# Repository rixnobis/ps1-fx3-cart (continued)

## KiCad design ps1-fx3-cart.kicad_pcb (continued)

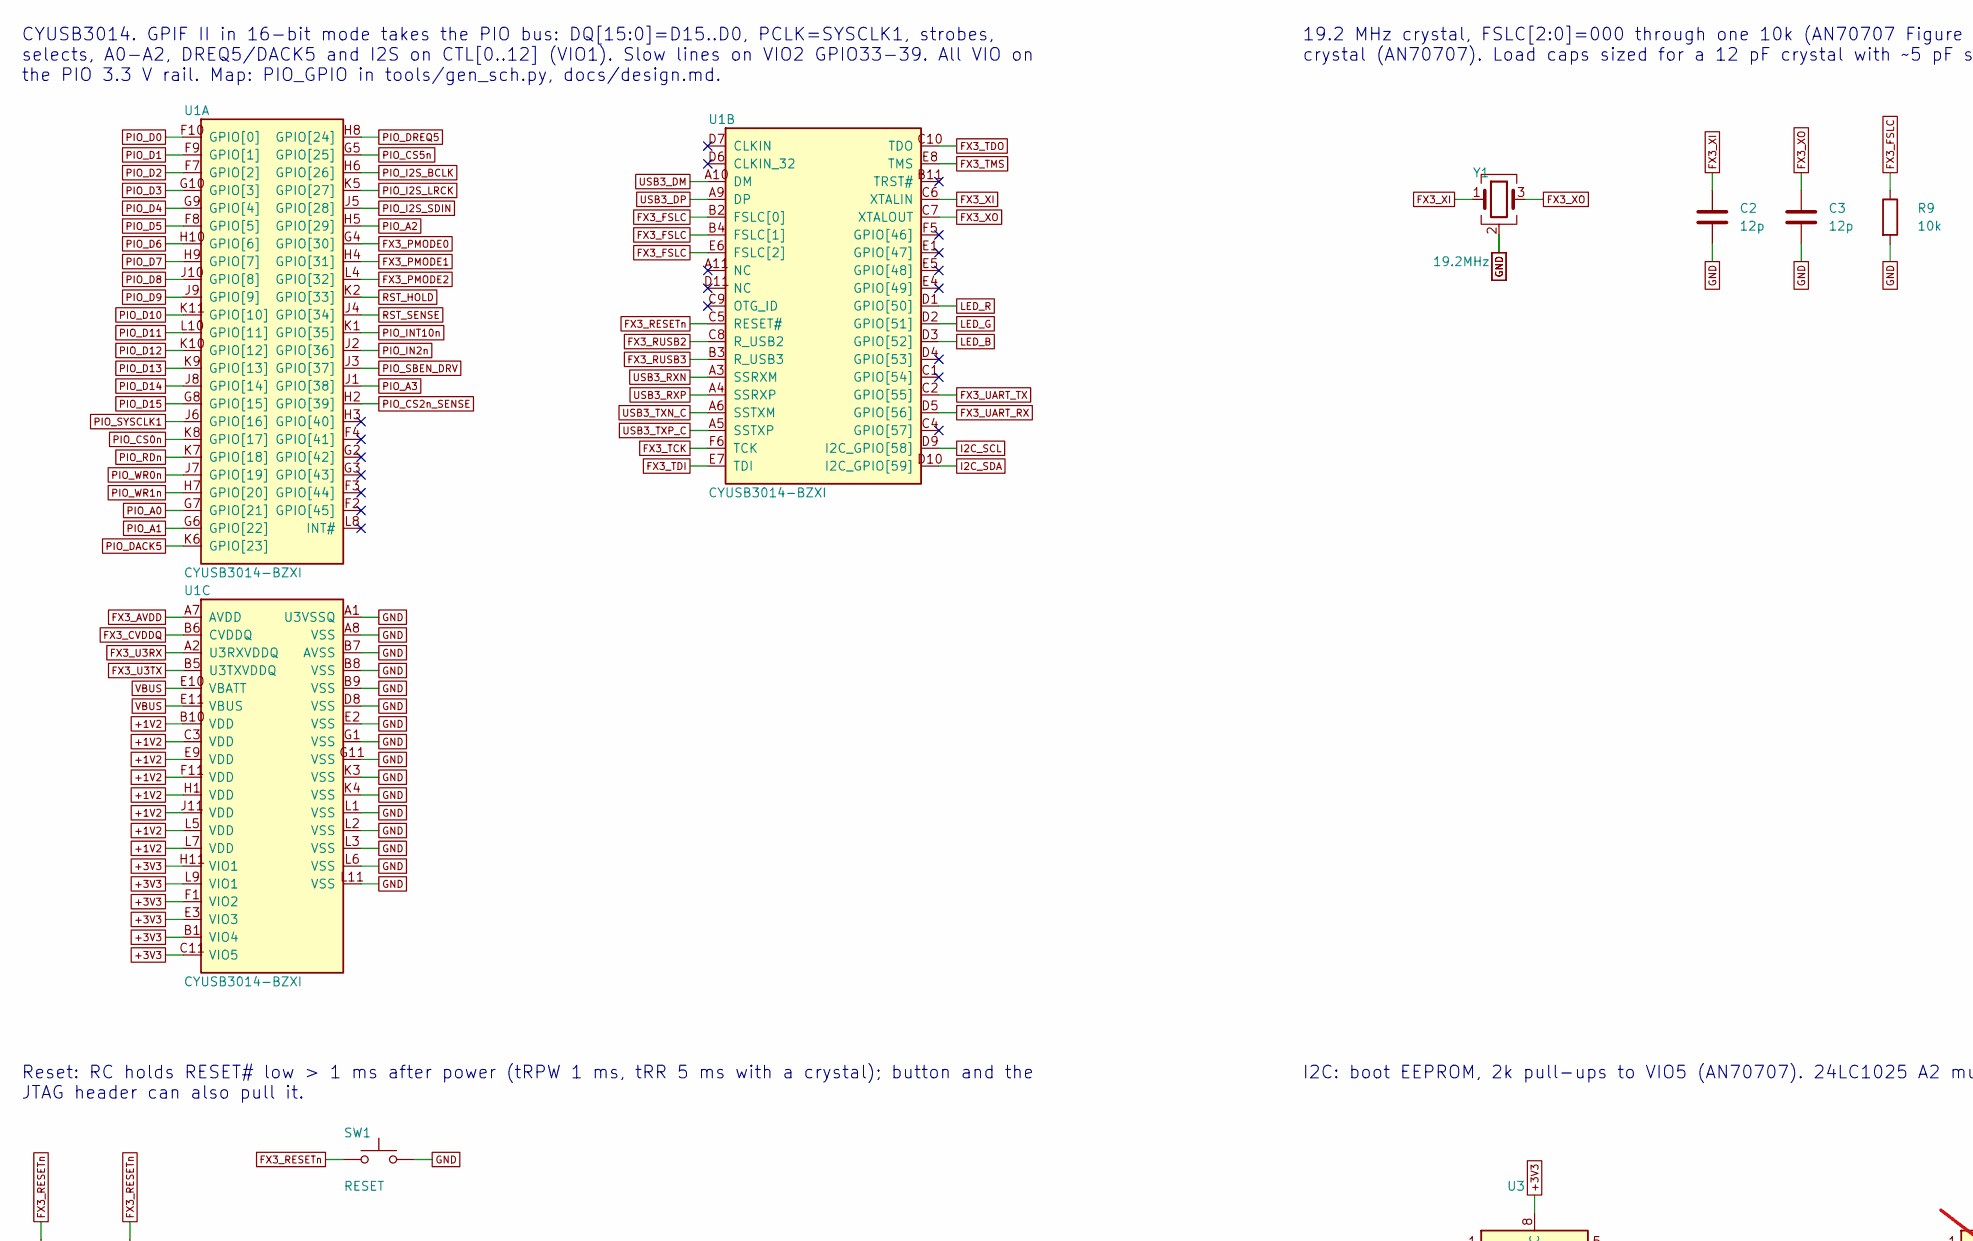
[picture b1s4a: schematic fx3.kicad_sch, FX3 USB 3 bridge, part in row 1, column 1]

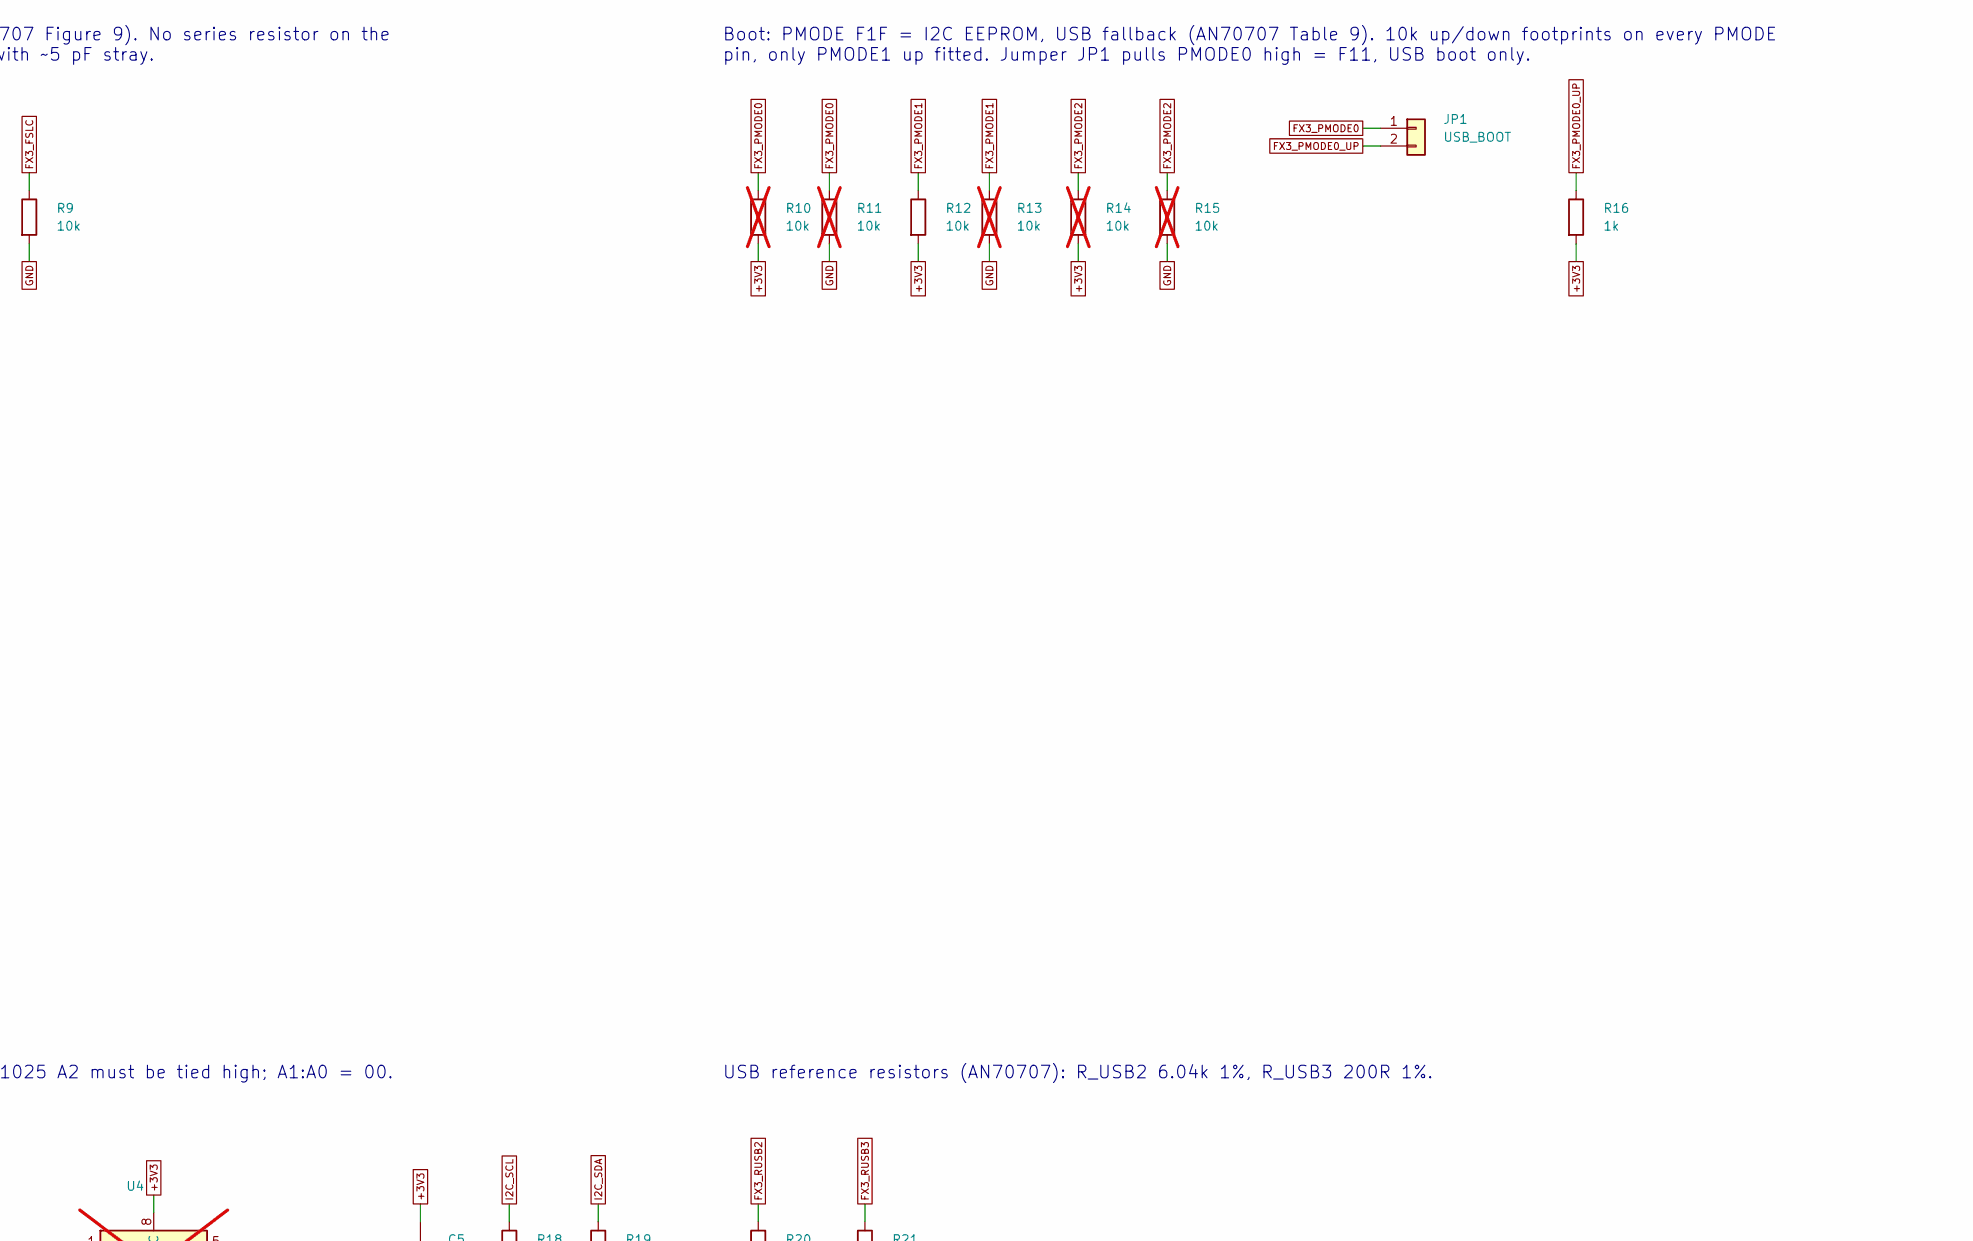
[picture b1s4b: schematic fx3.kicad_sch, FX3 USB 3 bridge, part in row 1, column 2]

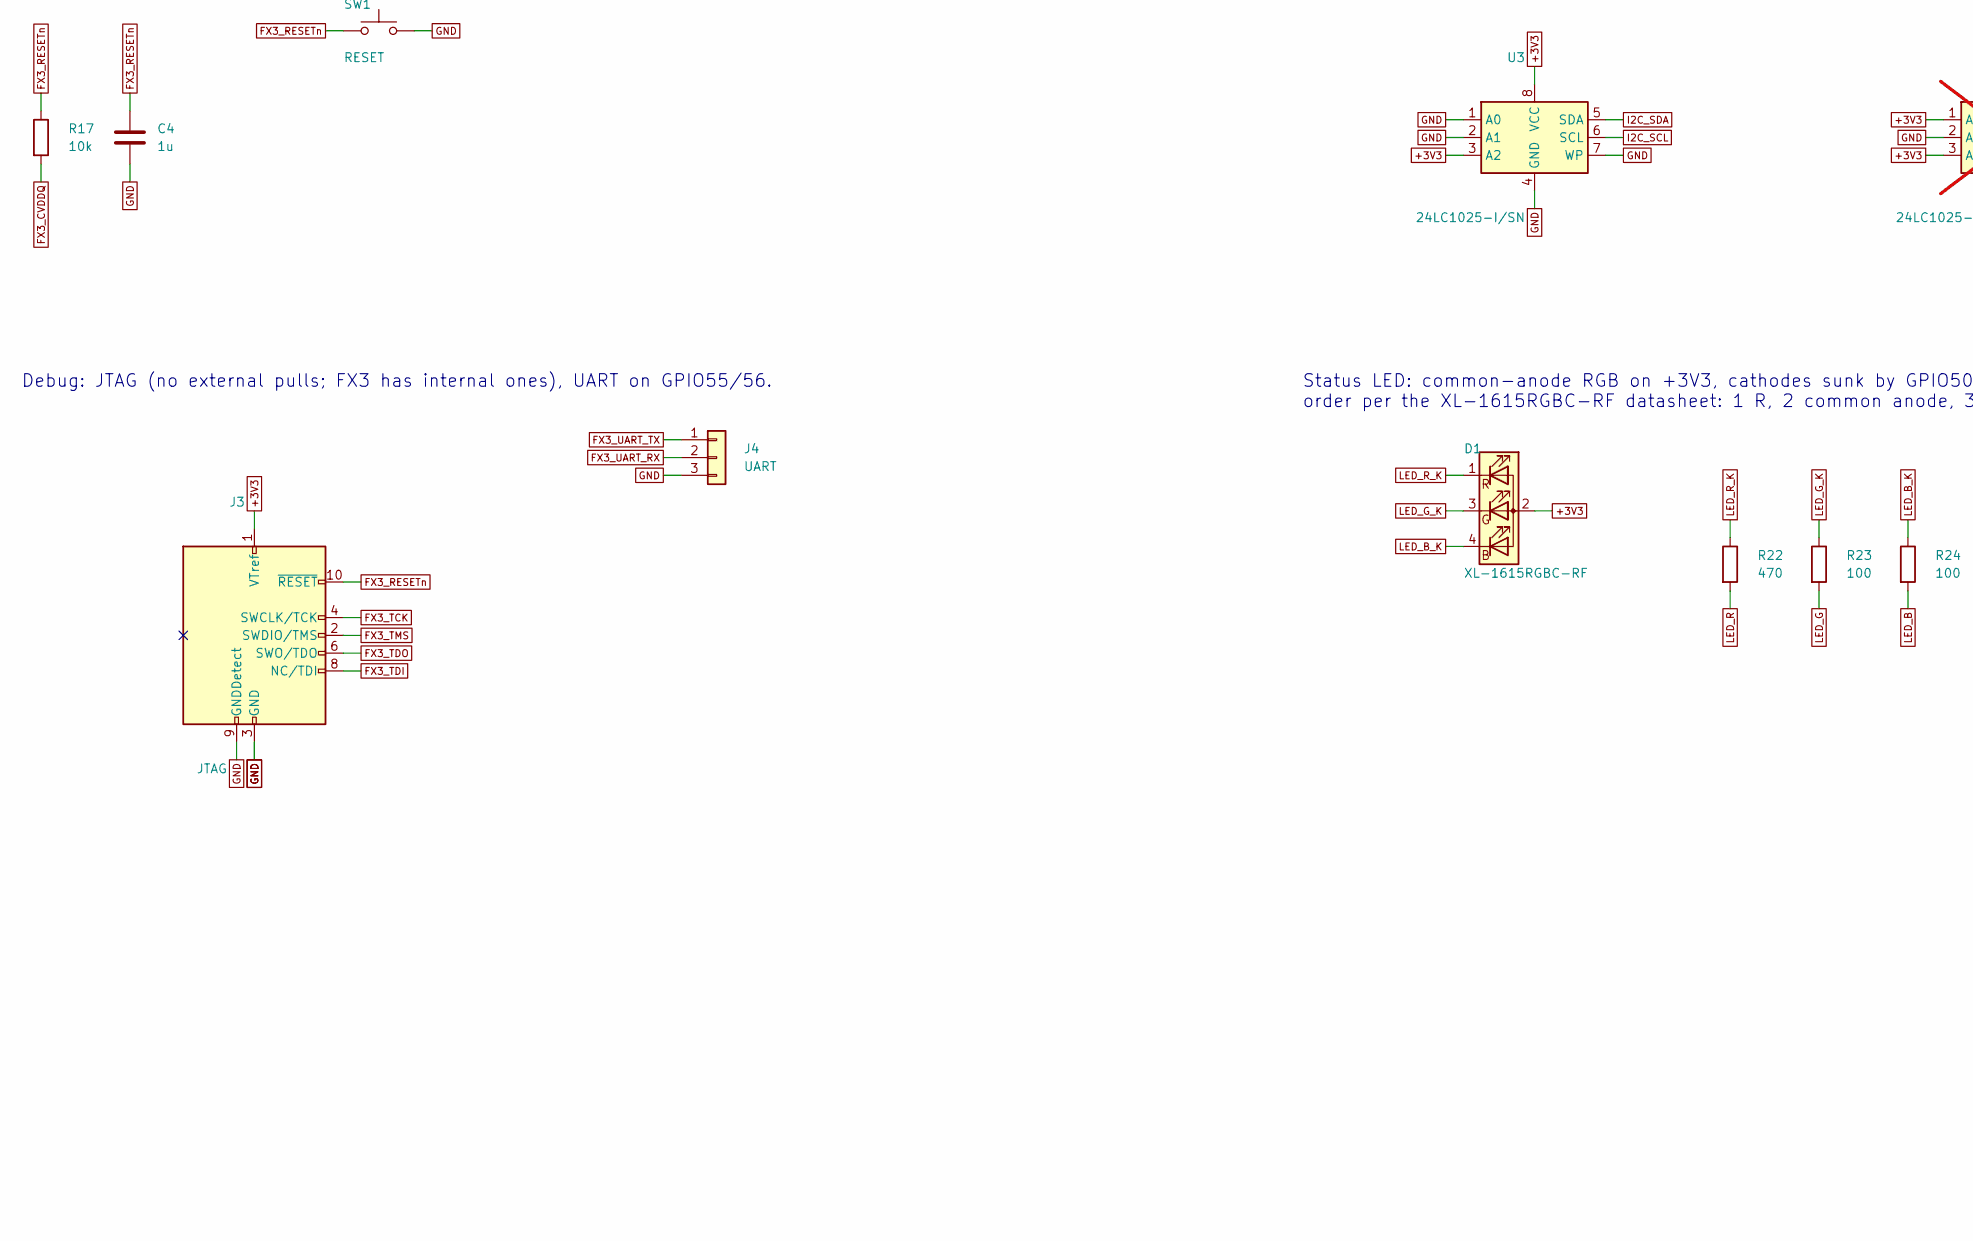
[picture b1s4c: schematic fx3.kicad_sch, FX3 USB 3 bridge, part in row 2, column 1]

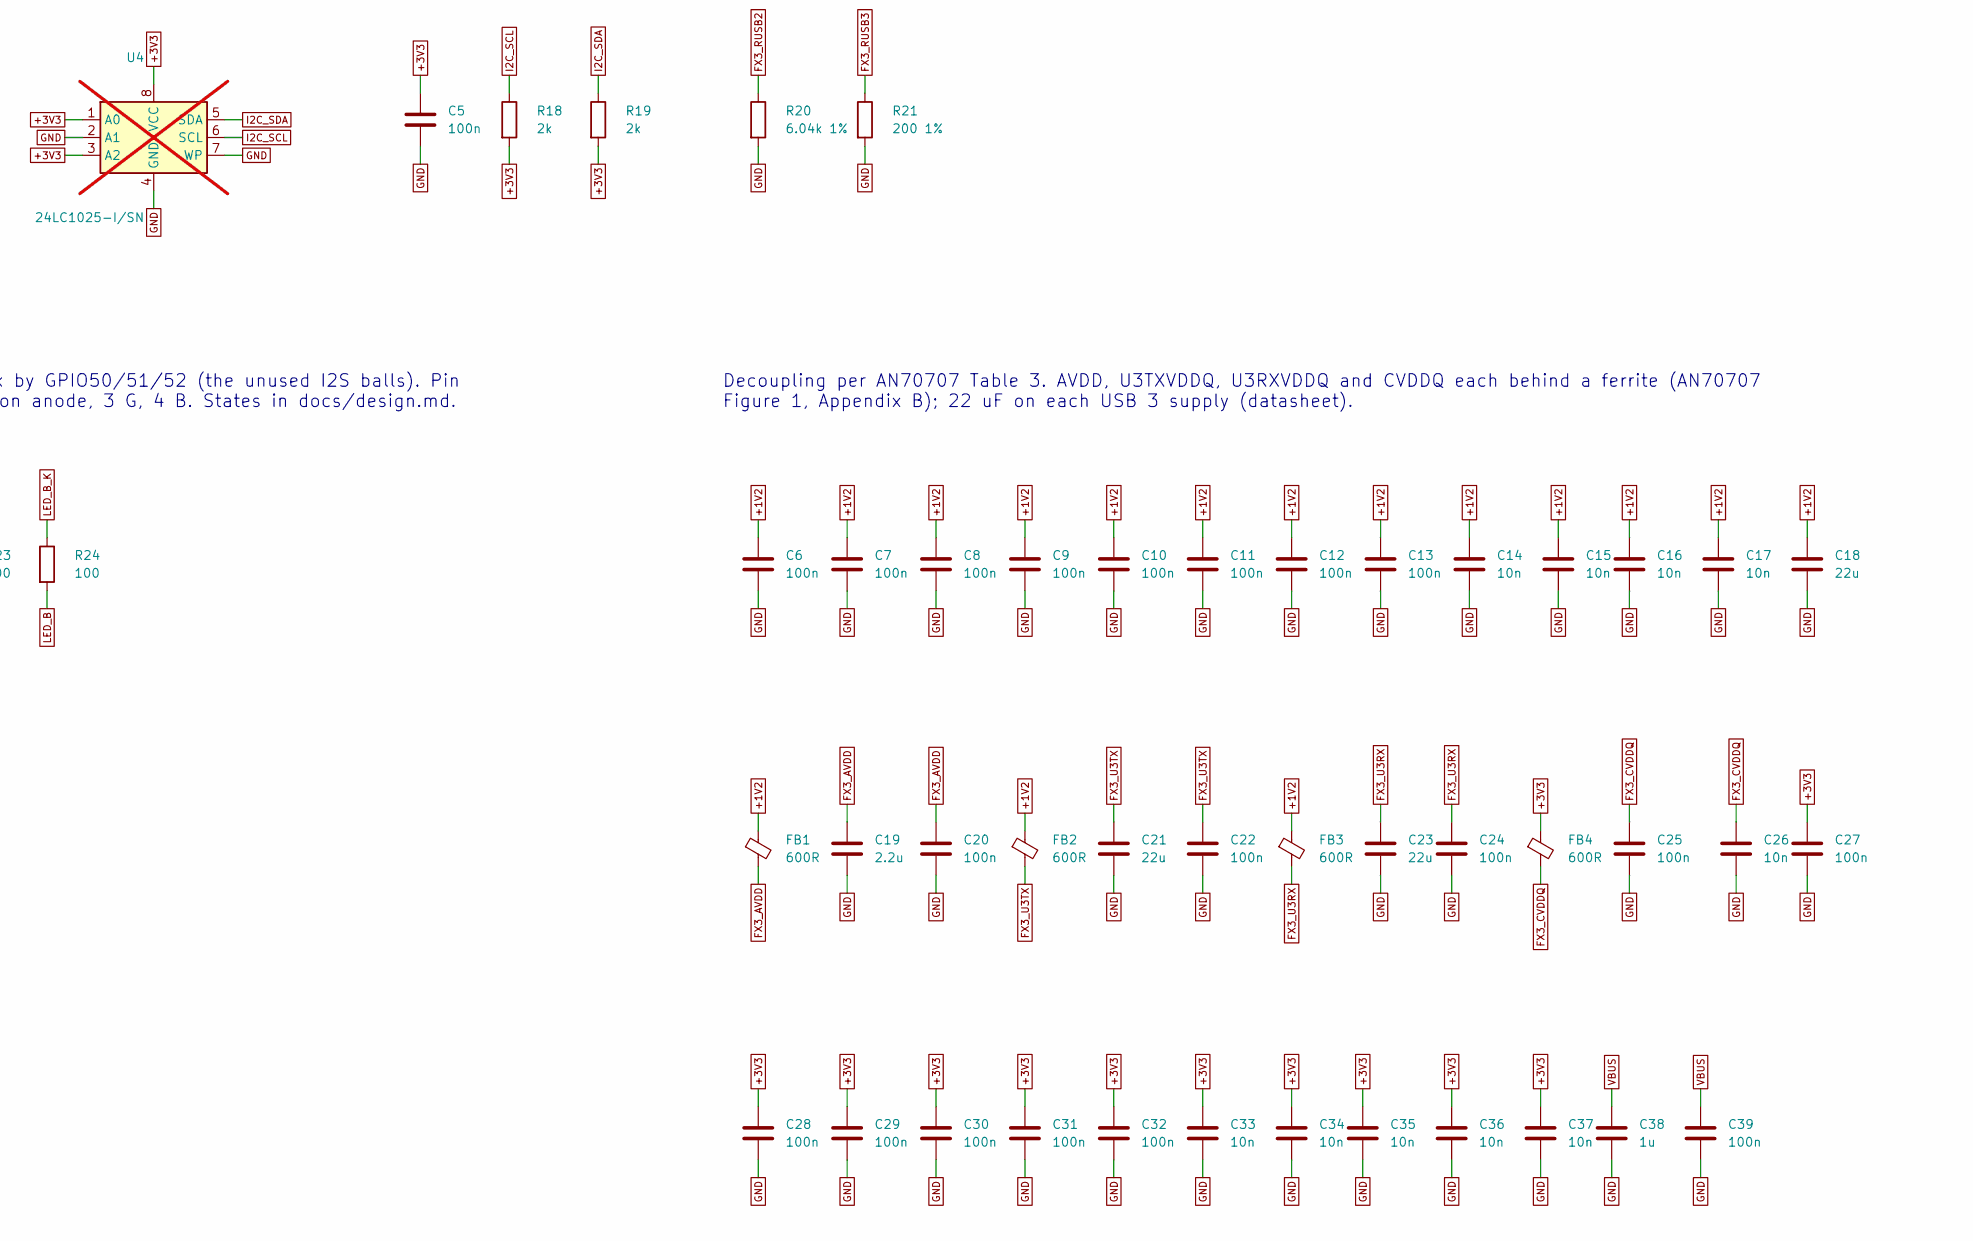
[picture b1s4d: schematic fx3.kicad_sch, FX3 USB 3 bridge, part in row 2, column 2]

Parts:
C2, C3: 12p; C_0402_1005Metric; LCSC C1547
C4, C38: 1u; C_0402_1005Metric; LCSC C52923
C5, C6, C7, C8, C9, C10, C11, C12, C13, C20, C22, C24, C25, C27, C28, C29, C30, C31, C32, C39: 100n; C_0402_1005Metric; LCSC C1525
C14, C15, C16, C17, C26, C33, C34, C35, C36, C37: 10n; C_0402_1005Metric; LCSC C15195
C18, C21, C23: 22u; C_0805_2012Metric; LCSC C45783
C19: 2.2u; C_0603_1608Metric; LCSC C23630
D1: XL-1615RGBC-RF; LED-ARRAY-SMD_4P-L1.6-W1.5-BR_XL-1615RGBC-RF; LCSC C965840
FB1, FB2, FB3, FB4: 600R; L_0603_1608Metric; LCSC C108301
J3: JTAG; PinHeader_2x05_P1.27mm_Vertical_SMD
J4: UART; PinHeader_1x03_P2.54mm_Vertical
JP1: USB_BOOT; PinHeader_1x02_P2.54mm_Vertical
R9, R12, R17: 10k; R_0402_1005Metric; LCSC C25744
R10, R11, R13, R14, R15: 10k; R_0402_1005Metric; LCSC C25744; not fitted
R16: 1k; R_0402_1005Metric; LCSC C11702
R18, R19: 2k; R_0402_1005Metric; LCSC C4109
R20: 6.04k 1%; R_0402_1005Metric; LCSC C97819
R21: 200 1%; R_0402_1005Metric; LCSC C25087
R22: 470; R_0402_1005Metric; LCSC C25117
R23, R24: 100; R_0402_1005Metric; LCSC C25076
SW1: RESET; SW_SPST_TL3342; LCSC C318884
U1: CYUSB3014-BZXI; BGA-121_L10.0-W10.0-R11-C11-P0.80-TL; LCSC C57294
U3: 24LC1025-I/SN; SOIC-8_3.9x4.9mm_P1.27mm; LCSC C615697
U4: 24LC1025-I/SN; SOIC-8_3.9x4.9mm_P1.27mm; LCSC C615697; not fitted
Y1: 19.2MHz; Crystal_SMD_3225-4Pin_3.2x2.5mm; LCSC C411225

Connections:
+1V2: C6.1, C7.1, C8.1, C9.1, C10.1, C11.1, C12.1, C13.1, C14.1, C15.1, C16.1, C17.1, C18.1, FB1.1, FB2.1, FB3.1, U1.B10 (VDD), U1.C3 (VDD), U1.E9 (VDD), U1.F11 (VDD), U1.H1 (VDD), U1.J11 (VDD), U1.L5 (VDD), U1.L7 (VDD); also elsewhere on the board
+3V3: C5.1, C27.1, C28.1, C29.1, C30.1, C31.1, C32.1, C33.1, C34.1, C35.1, C36.1, C37.1, D1.2 (A), FB4.1, J3.1 (VTref), R10.2, R12.2, R14.2, R16.2, R18.2, R19.2, U1.B1 (VIO4), U1.C11 (VIO5), U1.E3 (VIO3), U1.F1 (VIO2), U1.H11 (VIO1), U1.L9 (VIO1), U3.3 (A2), U3.8 (VCC), U4.1 (A0), U4.3 (A2), U4.8 (VCC); also elsewhere on the board
FX3_AVDD: C19.1, C20.1, FB1.2, U1.A7 (AVDD)
FX3_CVDDQ: C25.1, C26.1, FB4.2, R17.2, U1.B6 (CVDDQ)
FX3_FSLC: R9.1, U1.B2 (FSLC[0]), U1.B4 (FSLC[1]), U1.E6 (FSLC[2])
FX3_PMODE0: JP1.1, R10.1, R11.1, U1.G4 (GPIO[30])
FX3_PMODE0_UP: JP1.2, R16.1
FX3_PMODE1: R12.1, R13.1, U1.H4 (GPIO[31])
FX3_PMODE2: R14.1, R15.1, U1.L4 (GPIO[32])
FX3_RESETn: C4.1, J3.10 (~RESET), R17.1, SW1.1, U1.C5 (RESET#)
FX3_RUSB2: R20.1, U1.C8 (R_USB2)
FX3_RUSB3: R21.1, U1.B3 (R_USB3)
FX3_TCK: J3.4 (SWCLK/TCK), U1.F6 (TCK)
FX3_TDI: J3.8 (NC/TDI), U1.E7 (TDI)
FX3_TDO: J3.6 (SWO/TDO), U1.C10 (TDO)
FX3_TMS: J3.2 (SWDIO/TMS), U1.E8 (TMS)
FX3_U3RX: C23.1, C24.1, FB3.2, U1.A2 (U3RXVDDQ)
FX3_U3TX: C21.1, C22.1, FB2.2, U1.B5 (U3TXVDDQ)
FX3_UART_RX: J4.2, U1.D5 (GPIO[56])
FX3_UART_TX: J4.1, U1.C2 (GPIO[55])
FX3_XI: C2.1, U1.C6 (XTALIN), Y1.1
FX3_XO: C3.1, U1.C7 (XTALOUT), Y1.3
GND: C2.2, C3.2, C4.2, C5.2, C6.2, C7.2, C8.2, C9.2, C10.2, C11.2, C12.2, C13.2, C14.2, C15.2, C16.2, C17.2, C18.2, C19.2, C20.2, C21.2, C22.2, C23.2, C24.2, C25.2, C26.2, C27.2, C28.2, C29.2, C30.2, C31.2, C32.2, C33.2, C34.2, C35.2, C36.2, C37.2, C38.2, C39.2, J3.3 (GND), J3.5 (GND), J3.9 (GNDDetect), J4.3, R9.2, R11.2, R13.2, R15.2, R20.2, R21.2, SW1.2, U1.A1 (U3VSSQ), U1.A8 (VSS), U1.B7 (AVSS), U1.B8 (VSS), U1.B9 (VSS), U1.D8 (VSS), U1.E2 (VSS), U1.G1 (VSS), U1.G11 (VSS), U1.K3 (VSS), U1.K4 (VSS), U1.L1 (VSS), U1.L2 (VSS), U1.L3 (VSS), U1.L6 (VSS), U1.L11 (VSS), U3.1 (A0), U3.2 (A1), U3.4 (GND), U3.7 (WP), U4.2 (A1), U4.4 (GND), U4.7 (WP), Y1.2 (G), Y1.4 (G); also elsewhere on the board
I2C_SCL: R18.1, U1.D9 (I2C_GPIO[58]), U3.6 (SCL), U4.6 (SCL)
I2C_SDA: R19.1, U1.D10 (I2C_GPIO[59]), U3.5 (SDA), U4.5 (SDA)
LED_B: R24.2, U1.D3 (GPIO[52])
LED_B_K: D1.4 (BK), R24.1
LED_G: R23.2, U1.D2 (GPIO[51])
LED_G_K: D1.3 (GK), R23.1
LED_R: R22.2, U1.D1 (GPIO[50])
LED_R_K: D1.1 (RK), R22.1
PIO_A0: U1.G7 (GPIO[21]); also elsewhere on the board
PIO_A1: U1.G6 (GPIO[22]); also elsewhere on the board
PIO_A2: U1.H5 (GPIO[29]); also elsewhere on the board
PIO_A3: U1.J1 (GPIO[38]); also elsewhere on the board
PIO_CS0n: U1.K8 (GPIO[17]); also elsewhere on the board
PIO_CS2n_SENSE: U1.H2 (GPIO[39]); also elsewhere on the board
PIO_CS5n: U1.G5 (GPIO[25]); also elsewhere on the board
PIO_D0: U1.F10 (GPIO[0]); also elsewhere on the board
PIO_D1: U1.F9 (GPIO[1]); also elsewhere on the board
PIO_D2: U1.F7 (GPIO[2]); also elsewhere on the board
PIO_D3: U1.G10 (GPIO[3]); also elsewhere on the board
PIO_D4: U1.G9 (GPIO[4]); also elsewhere on the board
PIO_D5: U1.F8 (GPIO[5]); also elsewhere on the board
PIO_D6: U1.H10 (GPIO[6]); also elsewhere on the board
PIO_D7: U1.H9 (GPIO[7]); also elsewhere on the board
PIO_D8: U1.J10 (GPIO[8]); also elsewhere on the board
PIO_D9: U1.J9 (GPIO[9]); also elsewhere on the board
PIO_D10: U1.K11 (GPIO[10]); also elsewhere on the board
PIO_D11: U1.L10 (GPIO[11]); also elsewhere on the board
PIO_D12: U1.K10 (GPIO[12]); also elsewhere on the board
PIO_D13: U1.K9 (GPIO[13]); also elsewhere on the board
PIO_D14: U1.J8 (GPIO[14]); also elsewhere on the board
PIO_D15: U1.G8 (GPIO[15]); also elsewhere on the board
PIO_DACK5: U1.K6 (GPIO[23]); also elsewhere on the board
PIO_DREQ5: U1.H8 (GPIO[24]); also elsewhere on the board
PIO_I2S_BCLK: U1.H6 (GPIO[26]); also elsewhere on the board
PIO_I2S_LRCK: U1.K5 (GPIO[27]); also elsewhere on the board
PIO_I2S_SDIN: U1.J5 (GPIO[28]); also elsewhere on the board
PIO_IN2n: U1.J2 (GPIO[36]); also elsewhere on the board
PIO_INT10n: U1.K1 (GPIO[35]); also elsewhere on the board
PIO_RDn: U1.K7 (GPIO[18]); also elsewhere on the board
PIO_SBEN_DRV: U1.J3 (GPIO[37]); also elsewhere on the board
PIO_SYSCLK1: U1.J6 (GPIO[16]); also elsewhere on the board
PIO_WR0n: U1.J7 (GPIO[19]); also elsewhere on the board
PIO_WR1n: U1.H7 (GPIO[20]); also elsewhere on the board
RST_HOLD: U1.K2 (GPIO[33]); also elsewhere on the board
RST_SENSE: U1.J4 (GPIO[34]); also elsewhere on the board
USB3_DM: U1.A10 (DM); also elsewhere on the board
USB3_DP: U1.A9 (DP); also elsewhere on the board
USB3_RXN: U1.A3 (SSRXM); also elsewhere on the board
USB3_RXP: U1.A4 (SSRXP); also elsewhere on the board
USB3_TXN_C: U1.A6 (SSTXM); also elsewhere on the board
USB3_TXP_C: U1.A5 (SSTXP); also elsewhere on the board
VBUS: C38.1, C39.1, U1.E10 (VBATT), U1.E11 (VBUS); also elsewhere on the board

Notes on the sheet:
CYUSB3014. GPIF II in 16-bit mode takes the PIO bus: DQ[15:0]=D15..D0, PCLK=SYSCLK1, strobes, selects, A0-A2, DREQ5/DACK5 and I2S on CTL[0..12] (VIO1). Slow lines on VIO2 GPIO33-39. All VIO on the PIO 3.3 V rail. Map: PIO_GPIO in tools/gen_sch.py, docs/design.md.
19.2 MHz crystal, FSLC[2:0]=000 through one 10k (AN70707 Figure 9). No series resistor on the crystal (AN70707). Load caps sized for a 12 pF crystal with ~5 pF stray.
Boot: PMODE F1F = I2C EEPROM, USB fallback (AN70707 Table 9). 10k up/down footprints on every PMODE pin, only PMODE1 up fitted. Jumper JP1 pulls PMODE0 high = F11, USB boot only.
Reset: RC holds RESET# low > 1 ms after power (tRPW 1 ms, tRR 5 ms with a crystal); button and the JTAG header can also pull it.
I2C: boot EEPROM, 2k pull-ups to VIO5 (AN70707). 24LC1025 A2 must be tied high; A1:A0 = 00.
USB reference resistors (AN70707): R_USB2 6.04k 1%, R_USB3 200R 1%.
Debug: JTAG (no external pulls; FX3 has internal ones), UART on GPIO55/56.
Status LED: common-anode RGB on +3V3, cathodes sunk by GPIO50/51/52 (the unused I2S balls). Pin order per the XL-1615RGBC-RF datasheet: 1 R, 2 common anode, 3 G, 4 B. States in docs/design.md.
Decoupling per AN70707 Table 3. AVDD, U3TXVDDQ, U3RXVDDQ and CVDDQ each behind a ferrite (AN70707 Figure 1, Appendix B); 22 uF on each USB 3 supply (datasheet).

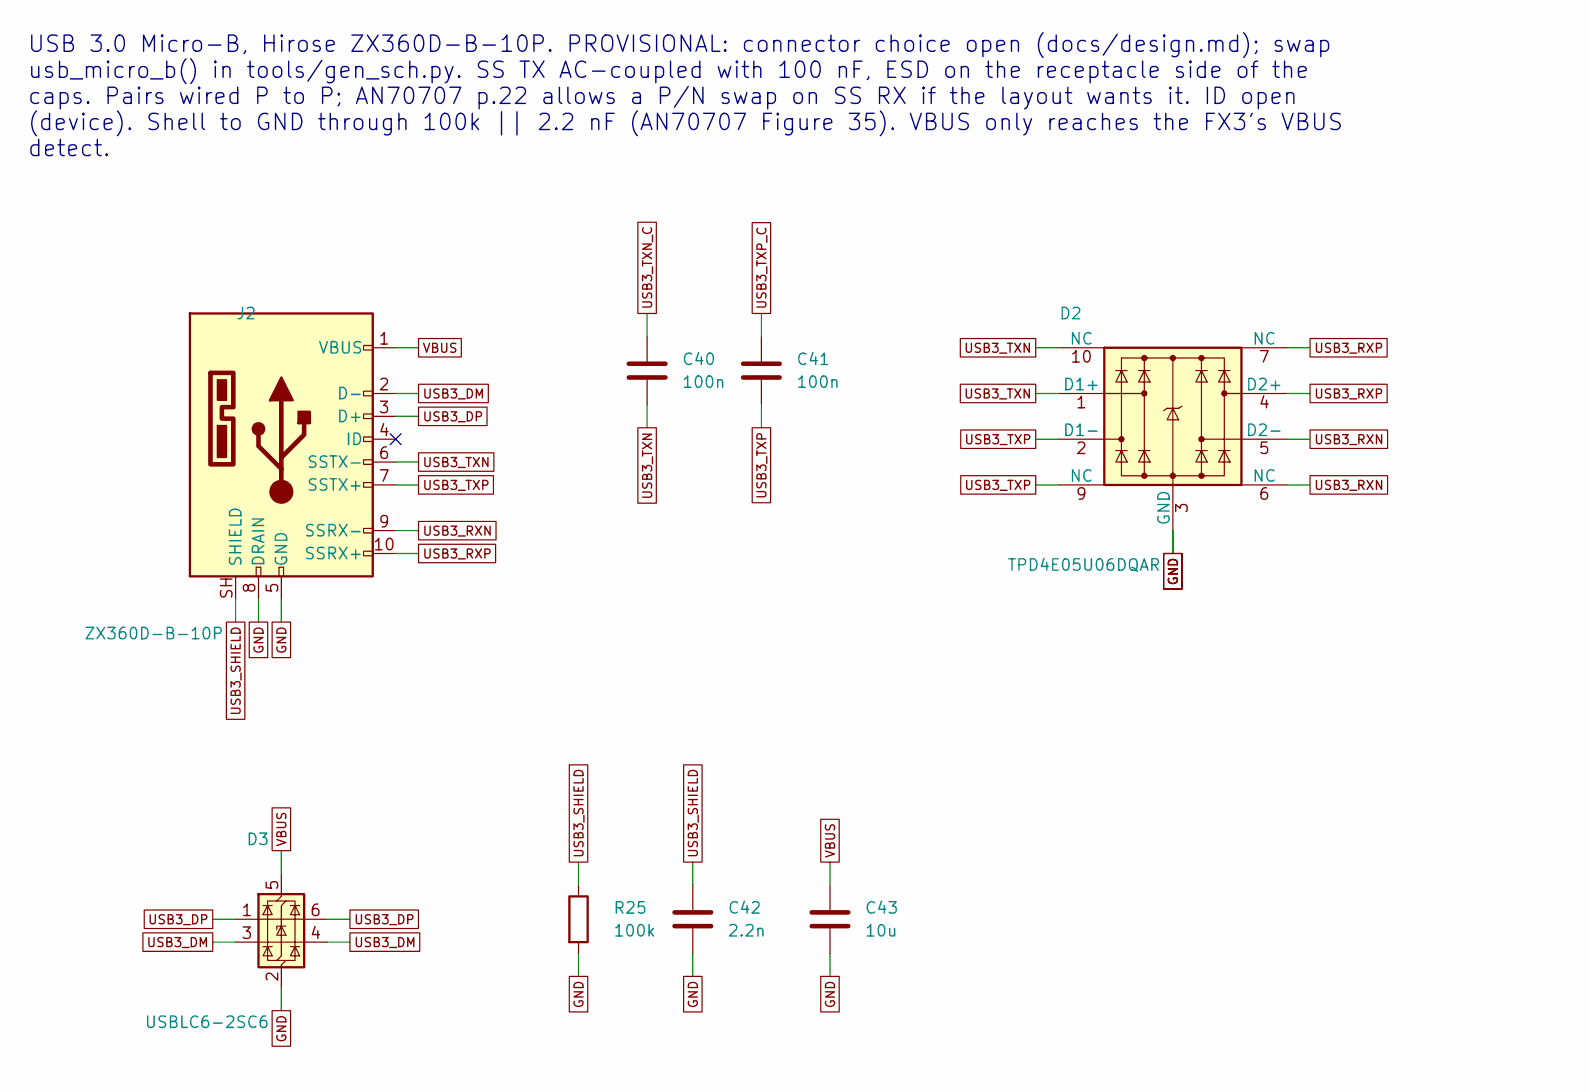
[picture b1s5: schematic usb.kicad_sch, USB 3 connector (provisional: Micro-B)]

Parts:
C40, C41: 100n; C_0402_1005Metric; LCSC C1525
C42: 2.2n; C_0402_1005Metric; LCSC C1531
C43: 10u; C_0603_1608Metric; LCSC C19702
D2: TPD4E05U06DQAR; USON-10_2.5x1.0mm_P0.5mm; LCSC C138714
D3: USBLC6-2SC6; SOT-23-6; LCSC C7519
J2: ZX360D-B-10P; USB-SMD_ZX360D-B-10P-30; LCSC C598201
R25: 100k; R_0402_1005Metric; LCSC C25741

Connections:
GND: C42.2, C43.2, D2.3 (GND), D2.8 (GND), D3.2 (GND), J2.5 (GND), J2.8 (DRAIN), R25.2; also elsewhere on the board
USB3_DM: D3.3 (I/O2), D3.4 (I/O2), J2.2 (D-); also elsewhere on the board
USB3_DP: D3.1 (I/O1), D3.6 (I/O1), J2.3 (D+); also elsewhere on the board
USB3_RXN: D2.5 (D2-), D2.6 (NC), J2.9 (SSRX-); also elsewhere on the board
USB3_RXP: D2.4 (D2+), D2.7 (NC), J2.10 (SSRX+); also elsewhere on the board
USB3_SHIELD: C42.1, J2.SH (SHIELD), R25.1
USB3_TXN: C40.2, D2.1 (D1+), D2.10 (NC), J2.6 (SSTX-)
USB3_TXN_C: C40.1; also elsewhere on the board
USB3_TXP: C41.2, D2.2 (D1-), D2.9 (NC), J2.7 (SSTX+)
USB3_TXP_C: C41.1; also elsewhere on the board
VBUS: C43.1, D3.5 (VBUS), J2.1 (VBUS); also elsewhere on the board

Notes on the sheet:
USB 3.0 Micro-B, Hirose ZX360D-B-10P. PROVISIONAL: connector choice open (docs/design.md); swap usb_micro_b() in tools/gen_sch.py. SS TX AC-coupled with 100 nF, ESD on the receptacle side of the caps. Pairs wired P to P; AN70707 p.22 allows a P/N swap on SS RX if the layout wants it. ID open (devic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

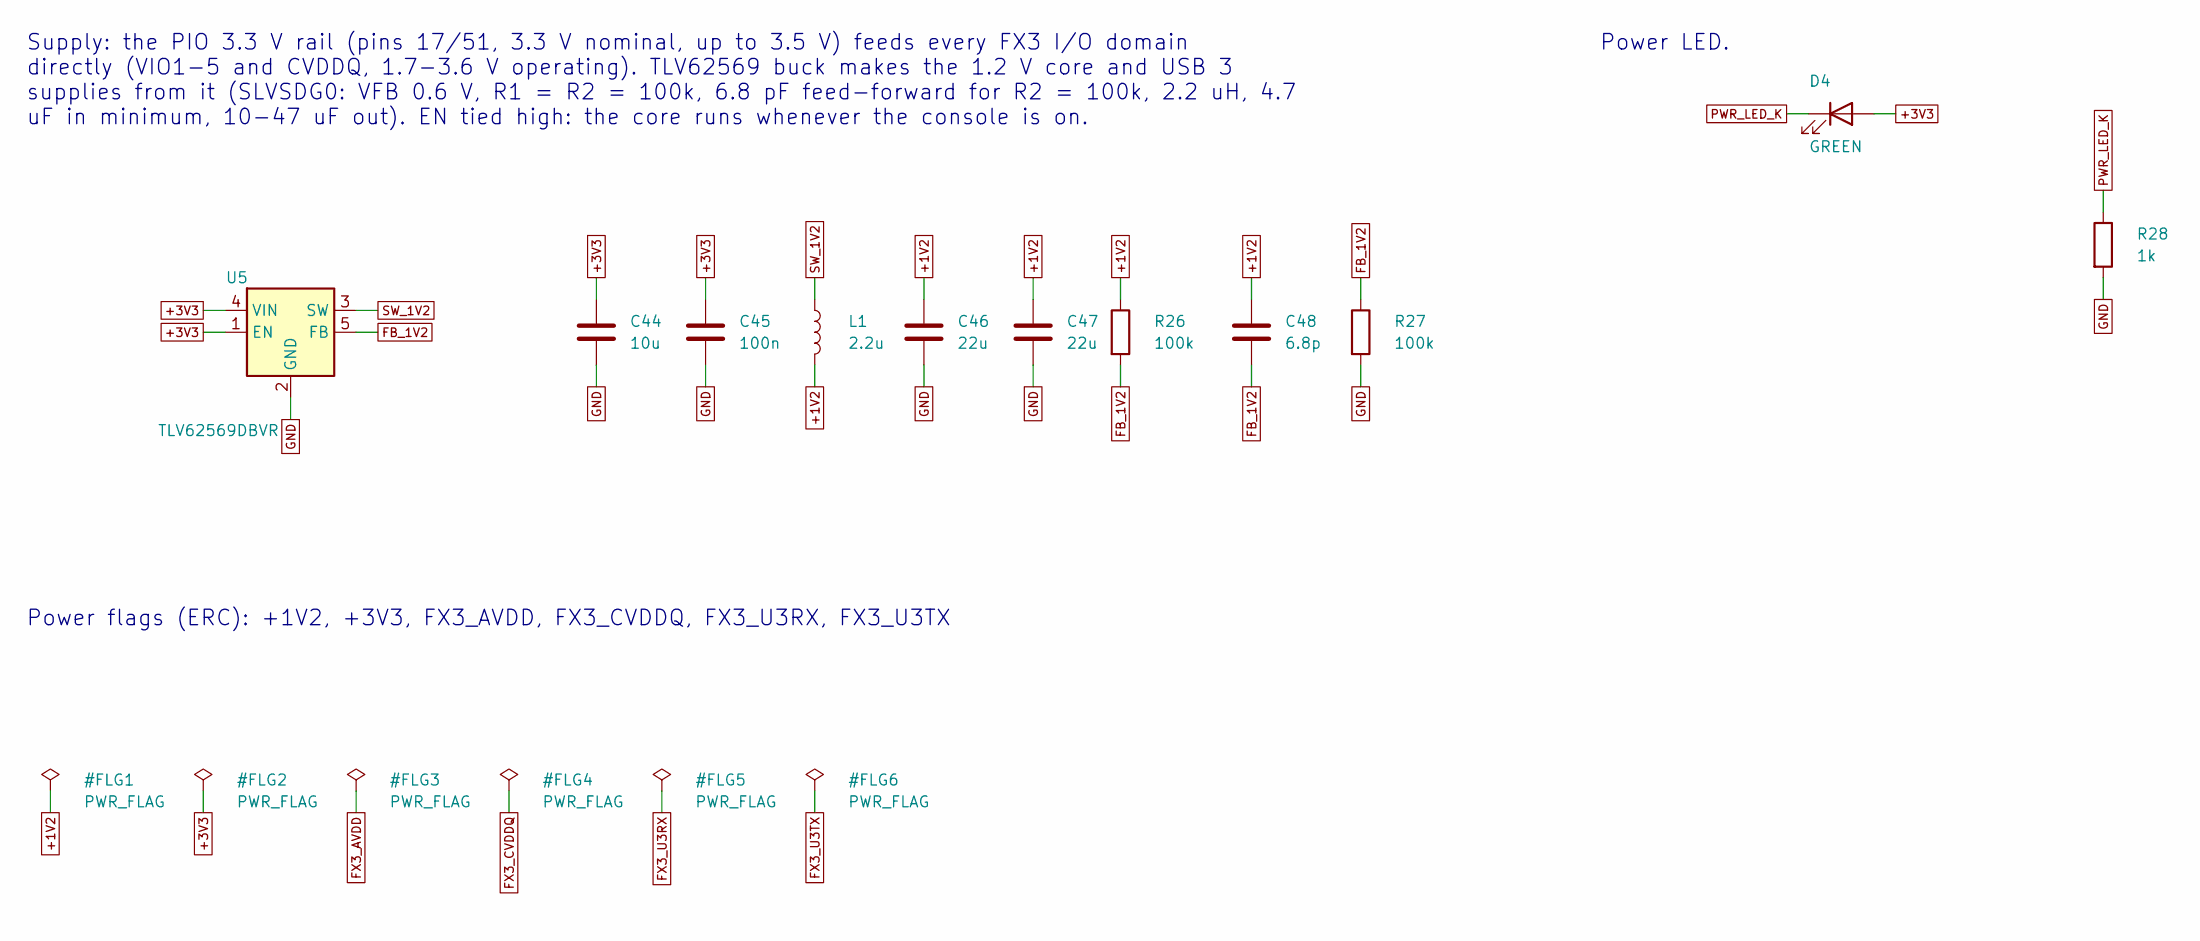
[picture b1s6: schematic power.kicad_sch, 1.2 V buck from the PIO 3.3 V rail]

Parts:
C44: 10u; C_0603_1608Metric; LCSC C19702
C45: 100n; C_0402_1005Metric; LCSC C1525
C46, C47: 22u; C_0805_2012Metric; LCSC C45783
C48: 6.8p; C_0402_1005Metric; LCSC C1576
D4: GREEN; LED_0603_1608Metric; LCSC C2986059
L1: 2.2u; L_Sunlord_SWPA4030S; LCSC C36409
R26, R27: 100k; R_0402_1005Metric; LCSC C25741
R28: 1k; R_0402_1005Metric; LCSC C11702
U5: TLV62569DBVR; SOT-23-5; LCSC C141836

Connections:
+1V2: C46.1, C47.1, C48.1, L1.2, R26.1; also elsewhere on the board
+3V3: C44.1, C45.1, D4.2 (A), U5.1 (EN), U5.4 (VIN); also elsewhere on the board
FB_1V2: C48.2, R26.2, R27.1, U5.5 (FB)
GND: C44.2, C45.2, C46.2, C47.2, R27.2, R28.2, U5.2 (GND); also elsewhere on the board
PWR_LED_K: D4.1 (K), R28.1
SW_1V2: L1.1, U5.3 (SW)

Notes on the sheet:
Supply: the PIO 3.3 V rail (pins 17/51, 3.3 V nominal, up to 3.5 V) feeds every FX3 I/O domain directly (VIO1-5 and CVDDQ, 1.7-3.6 V operating). TLV62569 buck makes the 1.2 V core and USB 3 supplies from it (SLVSDG0: VFB 0.6 V, R1 = R2 = 100k, 6.8 pF feed-forward for R2 = 100k, 2.2 uH, 4.7 uF in mi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
Power LED.
Power flags (ERC): +1V2, +3V3, FX3_AVDD, FX3_CVDDQ, FX3_U3RX, FX3_U3TX

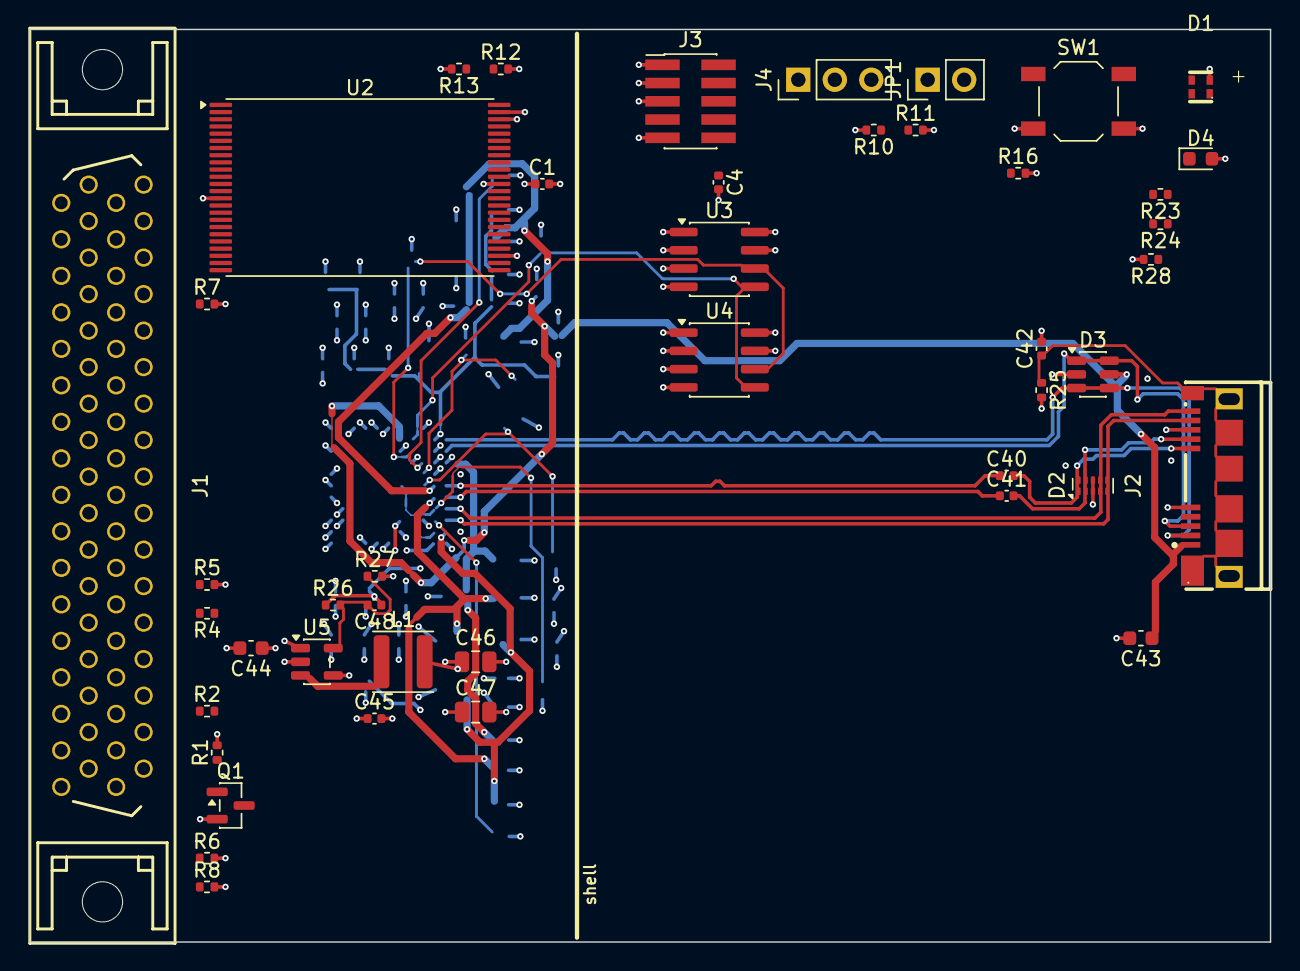
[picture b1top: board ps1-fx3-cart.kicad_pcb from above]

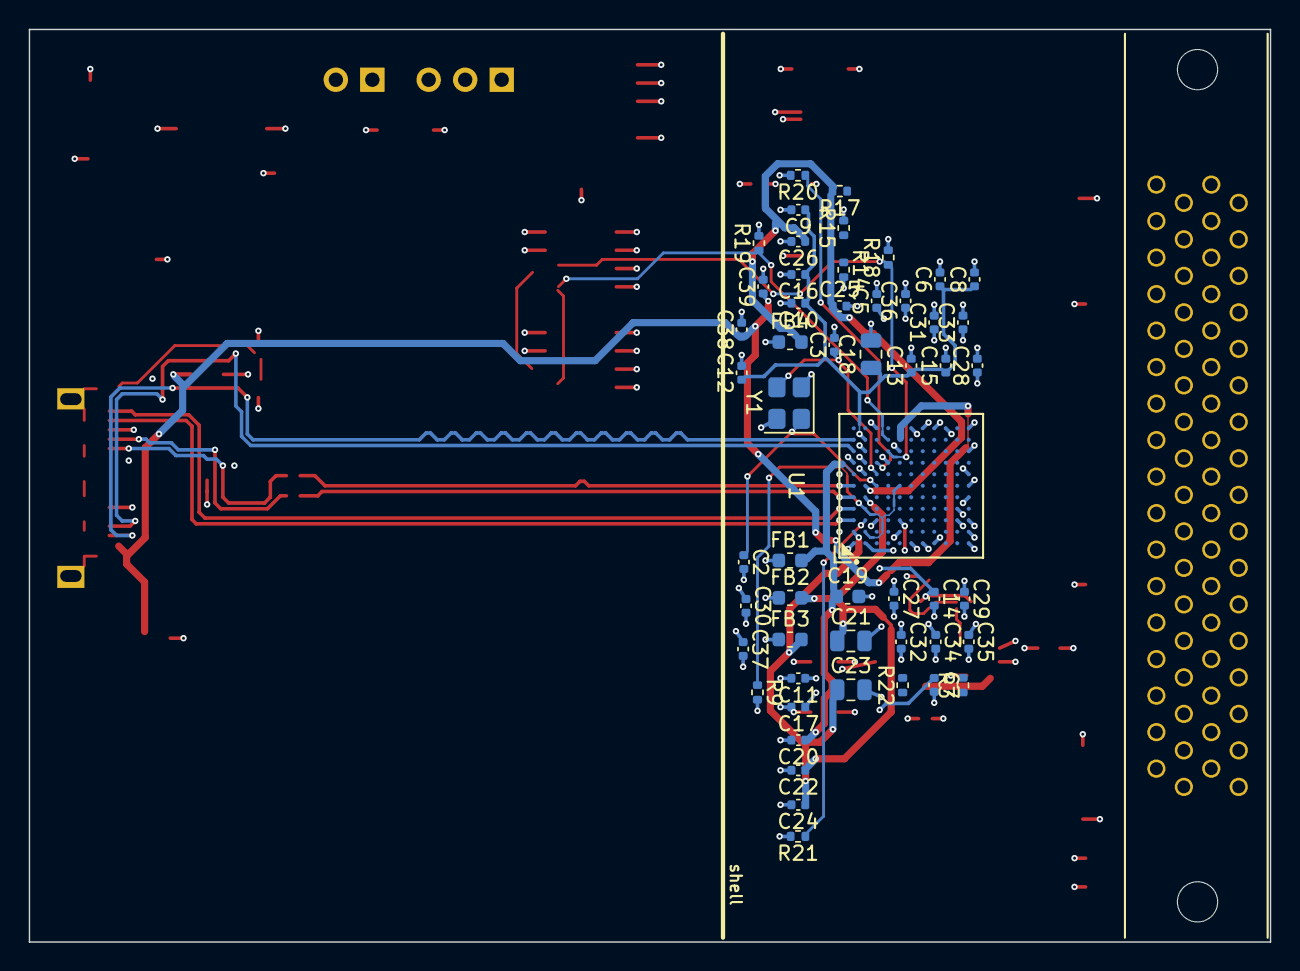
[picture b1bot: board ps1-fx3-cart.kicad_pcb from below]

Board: 4 copper layers, 86.4 x 63.5 mm, 98 parts (53 on the bottom side), 101 nets.

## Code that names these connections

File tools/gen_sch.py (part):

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# PIO connector, console rear-view numbering: 1-34 one side, 35-68 the other (psx-spx expansion
# port pinout; the pad numbers of pixel.lbr's PIOCONN carry the same signals).
# pin: (symbol pin name, net). DREQ5 and DACK5 are active high (psx-spx), the rest as named.
PIO_PINS = {2: ("~{RESET}", "PIO_RESETn"), 3: ("DREQ5", "PIO_DREQ5"), 36: ("DACK5", "PIO_DACK5"),
            4: ("~{CS0}", "PIO_CS0n"), 5: ("SBEN", "PIO_SBEN"), 39: ("~{CS2}", "PIO_CS2n"),
            30: ("~{RD}", "PIO_RDn"), 64: ("~{WR0}", "PIO_WR0n"), 38: ("~{WR1}", "PIO_WR1n"),
            37: ("~{IRQ10}", "PIO_INT10n"), 31: ("~{IRQ2}", "PIO_IN2n"), 65: ("~{CS5}", "PIO_CS5n"),
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# the console-clocked I2S on CTL[0..12]. VIO2 GPIOs carry the slow lines. The reset gate is on
# GPIO33, which the boot ROM leaves tristated in both USB and I2C boot (AN76405 Table 30), and
# nothing here sits on GPIO42/45/51/53/55, which the boot ROM drives.
PIO_GPIO = {16: "PIO_SYSCLK1",
            17: "PIO_CS0n", 18: "PIO_RDn", 19: "PIO_WR0n", 20: "PIO_WR1n", 21: "PIO_A0", 22: "PIO_A1",
            23: "PIO_DACK5", 24: "PIO_DREQ5", 25: "PIO_CS5n", 26: "PIO_I2S_BCLK", 27: "PIO_I2S_LRCK",
            28: "PIO_I2S_SDIN", 29: "PIO_A2",
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        fx3_nets[b] = f"PIO_D{k}" if k <= 15 else PIO_GPIO.get(k)
        continue
    fx3_nets[b] = {
        "I2C_GPIO[58]": "I2C_SCL", "I2C_GPIO[59]": "I2C_SDA", "INT#": None, "NC": None,
        "CLKIN": None, "CLKIN_32": None, "OTG_ID": None, "TRST#": None,
        "FSLC[0]": "FX3_FSLC", "FSLC[1]": "FX3_FSLC", "FSLC[2]": "FX3_FSLC",
        "RESET#": "FX3_RESETn", "XTALIN": "FX3_XI", "XTALOUT": "FX3_XO",
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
